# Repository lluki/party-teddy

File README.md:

This project turns a boring lullaby playing toy into a veritable party machine.
Videos and pictures can be found on [hackaday.io](https://hackaday.io/project/175761-party-teddy/details/185859)

It uses an ESP8266, drives the speaker via a transistor and 8 WS2812 LEDs

The software is written in Arduino and uses the [ESP8266 Audio](https://github.com/earlephilhower/ESP8266Audio)
library.

### Hardware
A custom board using an ESP8266 12E, the schematics can be found [here](https://github.com/lluki/party-teddy/blob/main/schema/schema.pdf)

### HTTP interface
At boot, the teddy will fetch /playlist which should return a single integer
describing how many songs can be fetched. Then it starts playing /songs/0.mp3,
if you push the button (that is mounted on the Teddys belly) it will loop to
/songs/1.mp3 etc. until it reaches the count described in playlist.

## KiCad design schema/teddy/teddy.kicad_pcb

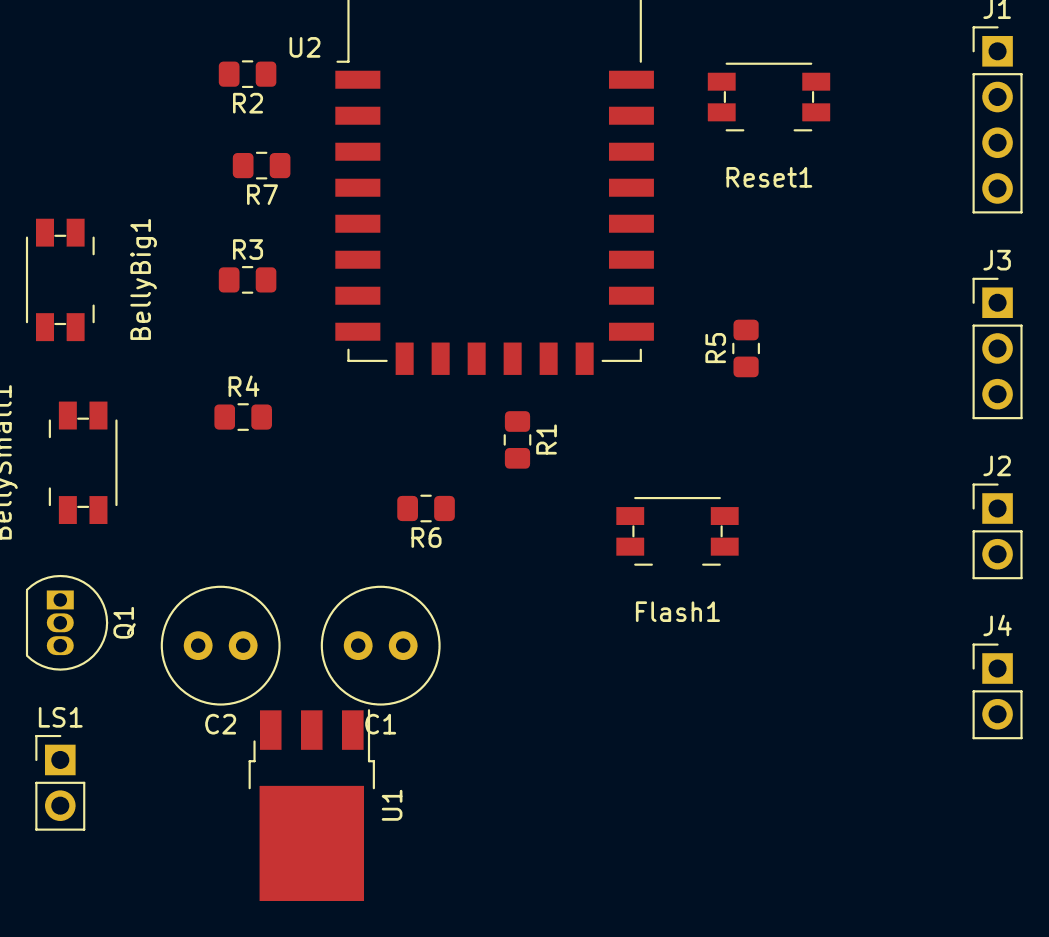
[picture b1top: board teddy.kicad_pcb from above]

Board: 2 copper layers, 21 parts (0 on the bottom side), 13 nets, no tracks yet.

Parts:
BellyBig1: SW_Push; Panasonic_EVQPUJ_EVQPUA
BellySmall1: SW_Push; Panasonic_EVQPUJ_EVQPUA
C1, C2: 10uF; C_Radial_D6.3mm_H11.0mm_P2.50mm
Flash1: SW_Push; Panasonic_EVQPUJ_EVQPUA
J1: Programming Header; PinHeader_1x04_P2.54mm_Vertical
J2: Speaker; PinHeader_1x02_P2.54mm_Vertical
J3: RGB LED; PinHeader_1x03_P2.54mm_Vertical
J4: Battery; PinHeader_1x02_P2.54mm_Vertical
LS1: Speaker; PinHeader_1x02_P2.54mm_Vertical
Q1: BC547; TO-92_Inline
R1, R2, R3, R6, R7: 10k; R_0805_2012Metric_Pad1.15x1.40mm_HandSolder
R4, R5: 1k; R_0805_2012Metric_Pad1.15x1.40mm_HandSolder
Reset1: SW_Push; Panasonic_EVQPUJ_EVQPUA
U1: TS2940-3.3; TO-252-3_TabPin2
U2: ESP-12E

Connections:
+3V3: C2.1, R1.2, R2.2, R3.2, R4.2, R7.2, U1.3, U2.8
+5V: C1.1, J1.4, J2.2, J3.3, J4.2, LS1.1, U1.1
/BELLY_BIG: BellyBig1.2, R3.1
/BELLY_SMALL: BellySmall1.2, R4.1
/FLASH: Flash1.2, J3.2, R1.1, U2.12
/RST: R2.1, Reset1.2, U2.1
/RX: J1.3, R5.2, U2.15
/SPK_OUT: J2.1, LS1.2, Q1.1
/TX: J1.2, U2.16
GND: BellyBig1.1, BellySmall1.1, C1.2, C2.2, Flash1.1, J1.1, J3.1, J4.1, Q1.3, R6.2, Reset1.1, U1.2, U2.9
unnamed: Q1.2, R5.1
unnamed: R6.1, U2.10
unnamed: R7.1, U2.3

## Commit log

2020-11-07 version 0 - this actually runs in the toy!
